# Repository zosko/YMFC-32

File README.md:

## What is YMFC-32

The YMFC-32 autonomous is an STM32 quadcopter flight controller that was programmed with the Arduino IDE. Its purpose is to create an educational project that can be used as a hobby or school project.

The main goals of this project are:

A bare minimum and understandable code
Try to keep the cost to a minimum

more datails here:
http://www.brokking.net/ymfc-32_auto_main.html

## Setup Arduino
- Search in `Boards Manager` for `Arduino SAM Boards 32bit` and install it
- Extract file `Arduino_STM32-master.zip` into `Arduino/hardware` folder.
- Select `STM32F103C series` from boards
- Variant to be `64k Flash`
- Upload method to be `Serial`
- CPU Speed to be `72Mhz`

## Testing GYRO
Quad | Should be
------|------
NOSE UP|positive PITCH
NOSE DOWN|negative PITCH
LEFT UP|positive ROLL
LEFT DOWN|negative ROLL
NOSE RIGHT|positive YAW
NOSE LEFT|negative YAW

## Kicad

PCB|3D View
-------|-------
|

## PCB Design

For PCB design i will use services from SeeedFusion. 

Seeed Fusion PCB Assembly Service offers one-stop prototyping for PCB manufacture, PCB assembly and as a result they produce superior quality PCBs and Fast Turnkey PCBA from 7 working days. When you prototype with Seeed Fusion, they can definitely provide Free DFA and Free functional tests for you! 

Check out their website to know about their manufacturing capabilities and service.
https://www.seeedstudio.com/prototype-pcb-assembly.html 

## Seeed Fusion PCBs
Empty PCB|Finished PCB
--------|--------
|

## Reasons to choose Seeed Studio
- They provide PCB services at extremely low pricing and with excellent quality.
- Their offer is structured in such a way that everyone may have these boards at a reasonable price.
- They have a highly knowledgeable crew that leads their clients to avail deals and guides them about the costs and rates of different services.
- A four-layer board with a comparable feature costs $5 for 10 pieces and is made in four days.
- SMT stencil with size (10cm x 13cm) is available for $8.00 per piece.

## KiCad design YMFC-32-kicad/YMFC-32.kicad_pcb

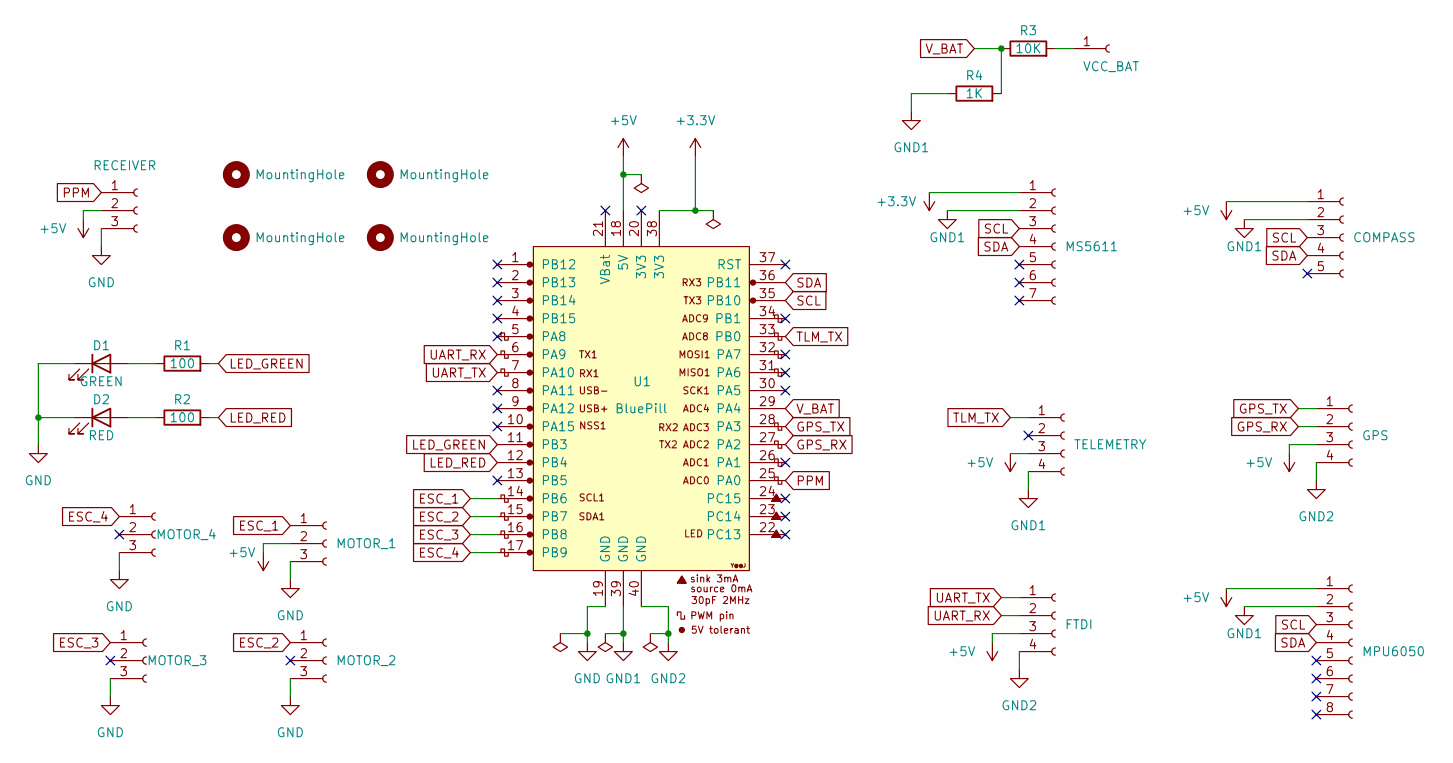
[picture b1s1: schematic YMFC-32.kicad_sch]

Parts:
D1: GREEN; LED_D5.0mm
D2: RED; LED_D5.0mm
H1, H2, H3, H4: MountingHole; MountingHole_3mm
J1: RECEIVER; PinHeader_1x03_P2.54mm_Vertical
J2: MOTOR_1; PinHeader_1x03_P2.54mm_Vertical
J3: MOTOR_2; PinHeader_1x03_P2.54mm_Vertical
J4: MOTOR_3; PinHeader_1x03_P2.54mm_Vertical
J5: MOTOR_4; PinHeader_1x03_P2.54mm_Vertical
J6: VCC_BAT; TestPoint_Pad_4.0x4.0mm
J7: TELEMETRY; PinHeader_1x04_P2.54mm_Vertical
J8: FTDI; PinHeader_1x04_P2.54mm_Vertical
J9: GPS; PinHeader_1x04_P2.54mm_Vertical
J10: MPU6050; PinHeader_1x08_P2.54mm_Vertical
J11: MS5611; PinHeader_1x07_P2.54mm_Vertical
J12: COMPASS; PinHeader_1x05_P2.54mm_Vertical
R1, R2: 100; R_Axial_DIN0309_L9.0mm_D3.2mm_P12.70mm_Horizontal
R3: 10K; R_Axial_DIN0309_L9.0mm_D3.2mm_P12.70mm_Horizontal
R4: 1K; R_Axial_DIN0309_L9.0mm_D3.2mm_P12.70mm_Horizontal
U1: BluePill; YAAJ_BluePill_1

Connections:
+3V3: J11.1, U1.38 (3V3)
+5V: J1.2, J2.2, J7.3, J8.3, J9.3, J10.1, J12.1, U1.18 (5V)
ESC_1: J2.1, U1.14 (PB6)
ESC_2: J3.1, U1.15 (PB7)
ESC_3: J4.1, U1.16 (PB8)
ESC_4: J5.1, U1.17 (PB9)
GND: D1.1 (K), D2.1 (K), J1.3, J2.3, J3.3, J4.3, J5.3, U1.19 (GND)
GND1: J7.4, J10.2, J11.2, J12.2, R4.1, U1.39 (GND)
GND2: J8.4, J9.4, U1.40 (GND)
GPS_RX: J9.2, U1.27 (PA2)
GPS_TX: J9.1, U1.28 (PA3)
LED_GREEN: R1.2, U1.11 (PB3)
LED_RED: R2.2, U1.12 (PB4)
unnamed: D1.2 (A), R1.1
unnamed: D2.2 (A), R2.1
unnamed: J6.1, R3.2
PPM: J1.1, U1.25 (PA0)
SCL: J10.3, J11.3, J12.3, U1.35 (PB10)
SDA: J10.4, J11.4, J12.4, U1.36 (PB11)
TLM_TX: J7.1, U1.33 (PB0)
UART_RX: J8.2, U1.6 (PA9)
UART_TX: J8.1, U1.7 (PA10)
V_BAT: R3.1, R4.2, U1.29 (PA4)

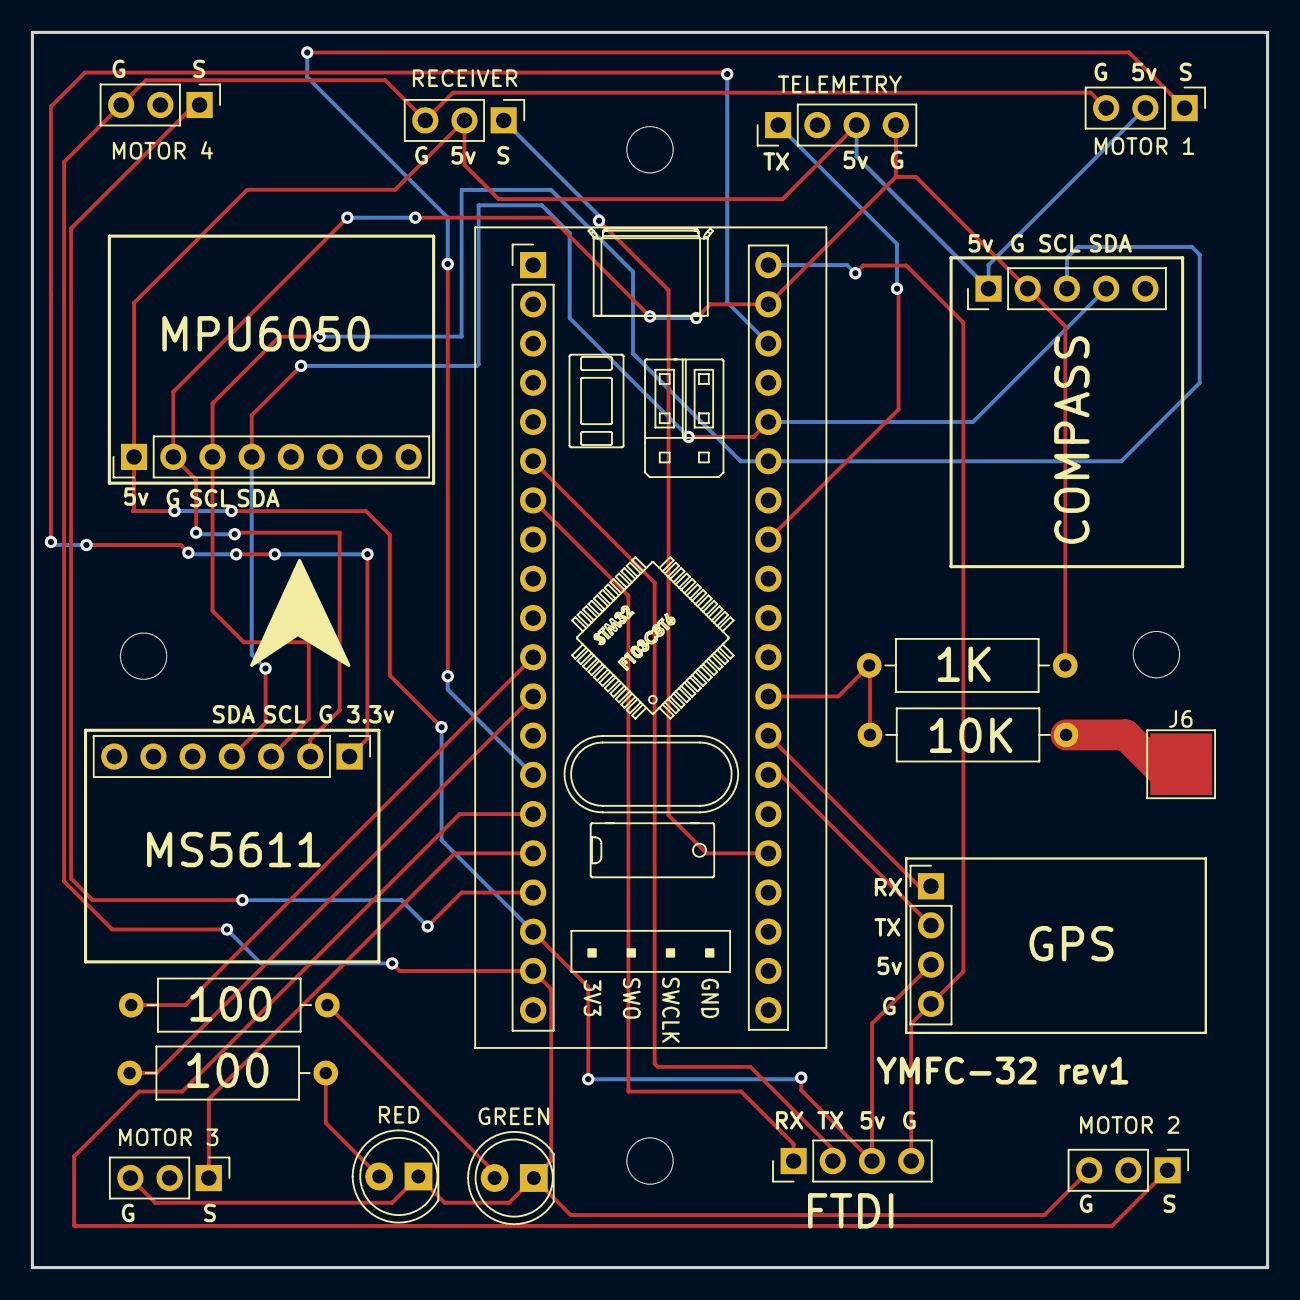
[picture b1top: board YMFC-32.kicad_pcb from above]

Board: 2 copper layers, 80.0 x 80.0 mm, 23 parts (0 on the bottom side), 23 nets.

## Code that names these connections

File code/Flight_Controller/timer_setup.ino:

///////////////////////////////////////////////////////////////////////////////////////////////////////////////////////////////////////
//In this file the timers for reading the receiver pulses and for creating the output ESC pulses are set.
///////////////////////////////////////////////////////////////////////////////////////////////////////////////////////////////////////
//More information can be found in these two videos:
//STM32 for Arduino - Connecting an RC receiver via input capture mode: https://youtu.be/JFSFbSg0l2M
//STM32 for Arduino - Electronic Speed Controller (ESC) - STM32F103C8T6: https://youtu.be/Nju9rvZOjVQ
///////////////////////////////////////////////////////////////////////////////////////////////////////////////////////////////////////
void timer_setup(void) {
  Timer2.attachCompare1Interrupt(handler_channel_1);
  TIMER2_BASE->CR1 = TIMER_CR1_CEN;
  TIMER2_BASE->CR2 = 0;
  TIMER2_BASE->SMCR = 0;
  TIMER2_BASE->DIER = TIMER_DIER_CC1IE;
  TIMER2_BASE->EGR = 0;
  TIMER2_BASE->CCMR1 = TIMER_CCMR1_CC1S_INPUT_TI1;
  TIMER2_BASE->CCMR2 = 0;
  TIMER2_BASE->CCER = TIMER_CCER_CC1E;

  //TIMER2_BASE->CCER |= TIMER_CCER_CC1P;    //Detect falling edge.
  TIMER2_BASE->CCER &= ~TIMER_CCER_CC1P; //Detect rising edge.
  TIMER2_BASE->PSC = 71;
  TIMER2_BASE->ARR = 0xFFFF;
  TIMER2_BASE->DCR = 0;

  TIMER4_BASE->CR1 = TIMER_CR1_CEN | TIMER_CR1_ARPE;
  TIMER4_BASE->CR2 = 0;
  TIMER4_BASE->SMCR = 0;
  TIMER4_BASE->DIER = 0;
  TIMER4_BASE->EGR = 0;
  TIMER4_BASE->CCMR1 = (0b110 << 4) | TIMER_CCMR1_OC1PE | (0b110 << 12) | TIMER_CCMR1_OC2PE;
  TIMER4_BASE->CCMR2 = (0b110 << 4) | TIMER_CCMR2_OC3PE | (0b110 << 12) | TIMER_CCMR2_OC4PE;
  TIMER4_BASE->CCER = TIMER_CCER_CC1E | TIMER_CCER_CC2E | TIMER_CCER_CC3E | TIMER_CCER_CC4E;
  TIMER4_BASE->PSC = 71;
  TIMER4_BASE->ARR = 5000;
  TIMER4_BASE->DCR = 0;
  TIMER4_BASE->CCR1 = 1000;

  TIMER4_BASE->CCR1 = 1000;
  TIMER4_BASE->CCR2 = 1000;
  TIMER4_BASE->CCR3 = 1000;
  TIMER4_BASE->CCR4 = 1000;
  pinMode(PB6, PWM);
  pinMode(PB7, PWM);
  pinMode(PB8, PWM);
  pinMode(PB9, PWM);
}

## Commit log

2022-02-26 add stm32 library
2022-02-26 add kicad
2022-02-26 add gerber files
2022-02-27 clean files
2022-04-20 rev1
